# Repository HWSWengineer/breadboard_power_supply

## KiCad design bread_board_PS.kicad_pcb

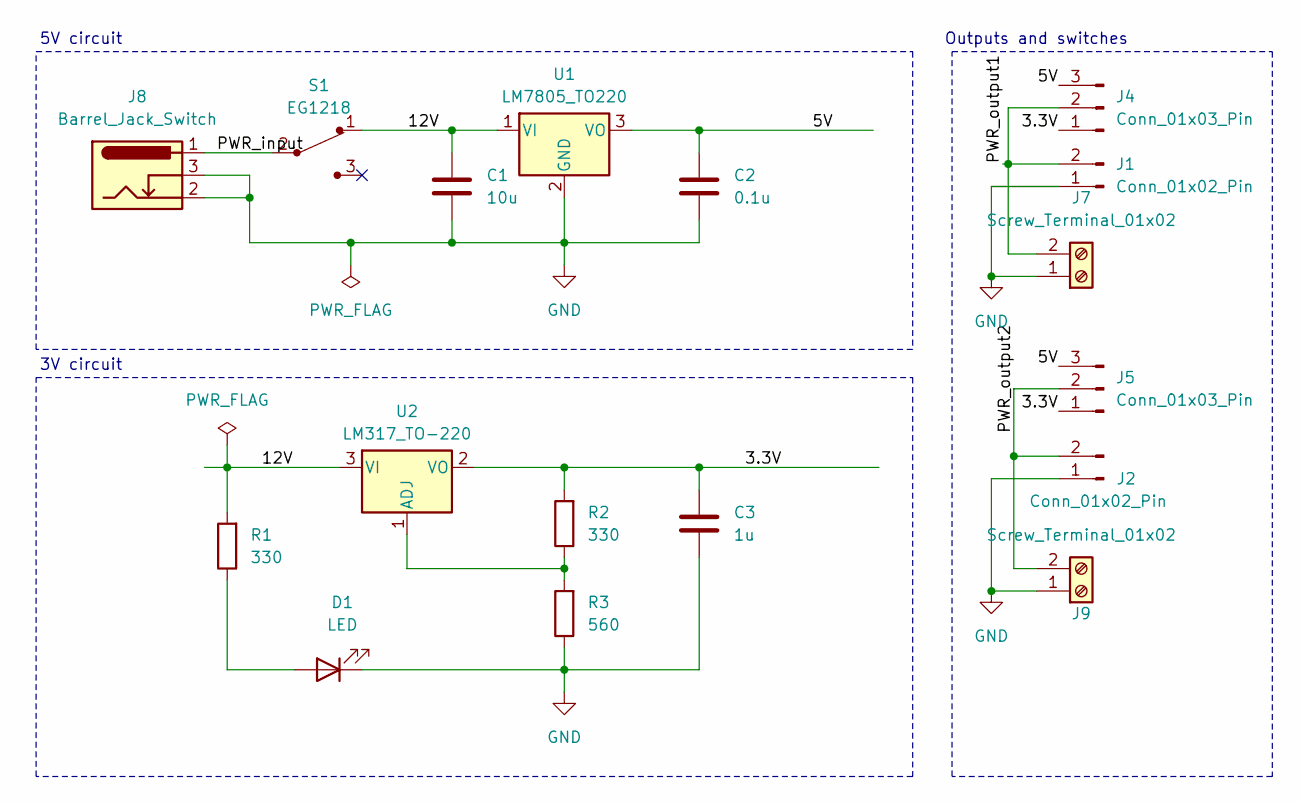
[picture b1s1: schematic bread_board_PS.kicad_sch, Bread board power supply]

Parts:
C1: 10u; C_Disc_D3.0mm_W1.6mm_P2.50mm
C2: 0.1u; C_Disc_D3.0mm_W1.6mm_P2.50mm
C3: 1u; C_Disc_D3.0mm_W1.6mm_P2.50mm
D1: LED; LED_D5.0mm
J1, J2: Conn_01x02_Pin; PinHeader_1x02_P2.54mm_Vertical
J4, J5: Conn_01x03_Pin; PinHeader_1x03_P2.54mm_Vertical
J7, J9: Screw_Terminal_01x02; TerminalBlock_bornier-2_P5.08mm
J8: Barrel_Jack_Switch; BarrelJack_Horizontal
R1, R2: 330; R_Axial_DIN0204_L3.6mm_D1.6mm_P7.62mm_Horizontal
R3: 560; R_Axial_DIN0204_L3.6mm_D1.6mm_P7.62mm_Horizontal
S1: EG1218; SW_1218_EWI; MPN EG1218; Digi-Key_PN EG1903-ND
U1: LM7805_TO220; TO-220-3_Vertical
U2: LM317_TO-220; TO-220-3_Vertical

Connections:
/3.3V: C3.1, J4.1, J5.1, R2.2, U2.2 (VO)
/5V: C2.1, J4.3, J5.3, U1.3 (VO)
/12V: C1.1, R1.2, S1.1, U1.1 (VI), U2.3 (VI)
/PWR_input: J8.1, S1.2
/PWR_output1: J1.2, J4.2, J7.2
/PWR_output2: J2.2, J5.2, J9.2
GND: C1.2, C2.2, C3.2, D1.1 (K), J1.1, J2.1, J7.1, J8.2, J8.3, J9.1, R3.1, U1.2 (GND)
unnamed: D1.2 (A), R1.1
unnamed: R2.1, R3.2, U2.1 (ADJ)

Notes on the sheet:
Outputs and switches
3V circuit
5V circuit

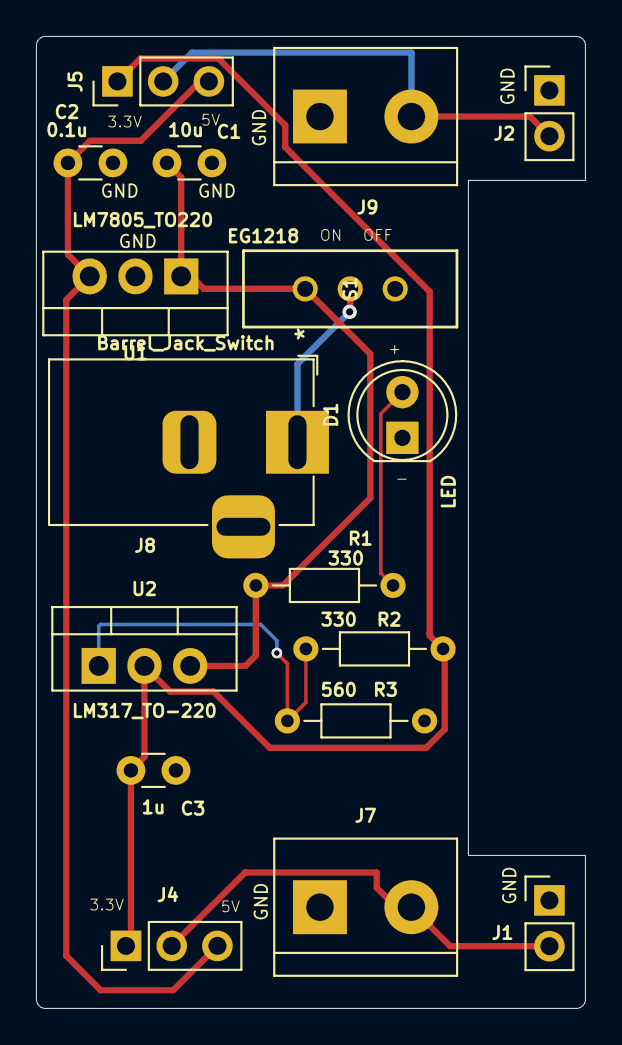
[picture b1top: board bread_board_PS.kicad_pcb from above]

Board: 2 copper layers, 30.5 x 54.0 mm, 17 parts (0 on the bottom side), 9 nets.
